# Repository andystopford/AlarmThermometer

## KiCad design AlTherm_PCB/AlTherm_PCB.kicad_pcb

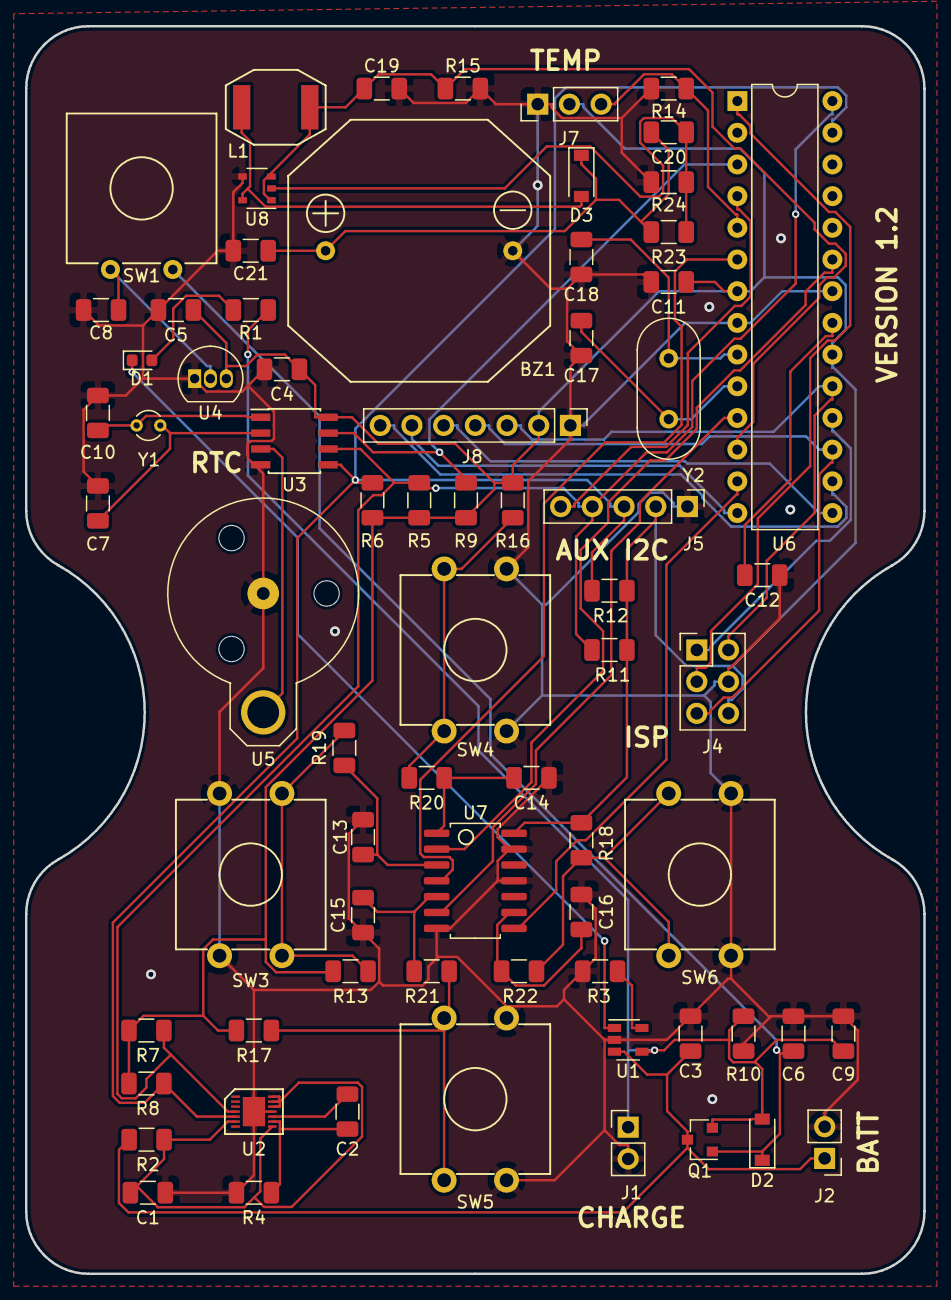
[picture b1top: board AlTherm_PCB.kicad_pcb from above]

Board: 2 copper layers, 72.0 x 100.0 mm, 72 parts (0 on the bottom side), 46 nets.

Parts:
BZ1: Buzzer; SMA21_pin
C1, C4, C11, C13, C14, C15, C16: 0.1uF; C_1206_3216Metric
C2: 0.47uF; C_1206_3216Metric
C3, C9: 4.7uF; C_1206_3216Metric
C5, C6, C8: 1uF; C_1206_3216Metric
C7, C10: 6.8pF; C_1206_3216Metric
C12: 0.1 uF; C_1206_3216Metric
C17, C18: 22pF; C_1206_3216Metric
C19: 10uF; C_1206_3216Metric
C20: 1.5nF; C_1206_3216Metric
C21: 33uF; C_1206_3216Metric
D1: LED; LED_0603_1608Metric
D2: B130-E3; D_SOD-123
D3: Diode_B130-E3; D_SOD-123
J1: Conn_charger; PinHeader_1x02_P2.54mm_Vertical
J2: Conn_Batt; PinHeader_1x02_P2.54mm_Vertical
J4: ISP1; PinHeader_2x03_P2.54mm_Vertical
J5: Conn_AUX; PinHeader_1x05_P2.54mm_Vertical
J7: Conn_TempSensor; PinHeader_1x03_P2.54mm_Vertical
J8: Conn_LCD; PinHeader_1x07_P2.54mm_Vertical
L1: 22uH; RS_Type16_Inductor
Q1: DMP1045U; SOT-23
R1: 470; R_1206_3216Metric
R2: 10; R_1206_3216Metric
R3, R23: 10K; R_1206_3216Metric
R4: 0.25; R_1206_3216Metric
R5, R6, R7, R8: 5k; R_1206_3216Metric
R9, R13, R16, R17, R18, R19, R20, R21, R22: 10k; R_1206_3216Metric
R10: 100K; R_1206_3216Metric
R11, R12: 1K; R_1206_3216Metric
R14: 4.7K; R_1206_3216Metric
R15: R_Small; R_1206_3216Metric
R24: 560; R_1206_3216Metric
SW1: Power Switch; SW_OnOff_12mm
SW3: SW_menu; SW_MOM_12mm
SW4: SW_up; SW_MOM_12mm
SW5: SW_down; SW_MOM_12mm
SW6: SW_select; SW_MOM_12mm
U1: MCP73831-2-OT; SOT-23-5
U2: MAX17201
U3: MCP7940N-xSN; SOIC-8_3.9x4.9mm_P1.27mm
U4: MCP1700; TO-92_Inline
U5: CR2032_cellHolder_PCB; BatteryHolder_Keystone_500
U6: ATmega328-PU; DIP-28_W7.62mm
U7: SN54HC14; SOIC-14W_4x8.75mm_P1.27mm
U8: NCP1403; TSOP-5_1.65x3.05mm_P0.95mm
Y1: 32.768kHz; Crystal_DS26_D2.0mm_L6.0mm_Vertical
Y2: Crystal 8MHz; Crystal_HC49-U_Vertical

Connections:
+1V5: U3.3, U5.1
/BZR: C19.1, L1.1, R15.1, U6.12, U8.1, U8.3
/CS: J8.7, U6.16
/DC: J8.6, U6.14
/DWN: U6.11, U7.6
/DWN_IN: C15.1, R21.2, U7.5
/INTI: J7.3, R14.1, U6.5
/INTO: J5.5, U6.4
/MFP: R9.2, U3.7, U6.3
/MISO: J4.1, U6.18
/MNU: U6.6, U7.4
/MNU_IN: C13.1, R19.2, U7.3
/MOSI: J4.5, J8.4, U6.17
/RES: J8.5, U6.15
/RESET: J4.3, U6.1
/SCK: J4.2, J8.3, U6.19
/SCL: J5.4, R5.2, R7.2, R11.2, U2.11, U3.6, U6.28
/SDA: J5.3, R6.2, R8.2, R12.2, U2.12, U3.5, U6.27
/SEL: U6.13, U7.8
/SEL_IN: C16.1, R22.2, U7.9
/UP: U6.23, U7.2
/UP_IN: C14.1, R20.2, U7.1
/XTAL1: C18.1, U6.9, Y2.2
/XTAL2: C17.1, U6.10, Y2.1
GND: BZ1.2, C1.2, C3.2, C4.2, C5.2, C6.2, C7.2, C8.2, C9.2, C10.2, C11.2, C12.2, C13.2, C14.2, C15.2, C16.2, C17.2, C18.2, C19.2, C21.2, J1.2, J2.2, J4.4, J5.1, J7.1, J8.1, R3.2, R4.1, R10.2, R14.2, R15.2, R24.2, SW3.1, SW4.1, SW5.1, SW6.1, U1.2, U2.4, U2.15, U3.4, U4.1, U5.2, U6.8, U6.22, U7.7, U7.11, U7.13, U8.4
unnamed: BZ1.1, C20.1, C21.1, D3.1, R23.1
unnamed: C1.1, R2.1, U2.1, U2.5, U2.6, U2.7, U2.13
unnamed: C2.1, U2.3
unnamed: C2.2, R4.2, U2.2
unnamed: C3.1, J2.1, Q1.3, R2.2, U1.3
unnamed: C6.1, D2.1, Q1.1, SW1.2
unnamed: C7.1, U3.2, Y1.1
unnamed: C8.1, SW1.1, U4.2
unnamed: C9.1, D2.2, J1.1, Q1.2, R1.1, R10.1, U1.4
unnamed: C10.1, U3.1, Y1.2
unnamed: C12.1, U6.21
unnamed: C20.2, R23.2, R24.1, U8.2
unnamed: D1.1, U1.1
unnamed: D1.2, R1.2
unnamed: D3.2, L1.2, U8.5
unnamed: R3.1, U1.5
unnamed: R13.2, R19.1, SW3.2
unnamed: R16.2, R20.1, SW4.2
unnamed: R17.2, R21.1, SW5.2
unnamed: R18.2, R22.1, SW6.2
VCC: C4.1, C5.1, C11.1, J4.6, J5.2, J7.2, J8.2, R5.1, R6.1, R7.1, R8.1, R9.1, R11.1, R12.1, R13.1, R16.1, R17.1, R18.1, U3.8, U4.3, U6.7, U6.20, U7.14

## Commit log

2019-01-09 Initial commit, PCB schematic and layout done, no routing
2019-05-08 Source sort of working, going to start again with state machine
2019-05-08 PCB final?
2019-05-12 State Machine
    SM working but not finished
2019-06-02 Menus set up and working, timer part set up.
2019-06-15 Source code functional, PCB final, but note comments in schematic
2019-06-22 Working; commit before non-RTC branch
2019-07-16 All working except RTC adjust, prior to class for timer menu
2020-02-25 Some tidying to code, esp setting RTC
2020-08-28 Working version - commit prior to PCB changes
